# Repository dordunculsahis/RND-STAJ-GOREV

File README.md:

# TRANSCIEVER-FOOTPRINT
SN65HVD10 RS485 Transceiver'in SMD ve Through Hole footprintleri 'TRANSCEİVER.pretty' klasörünün içindedir

Transceiver'in schematic kütüphanesi 'TRANSCEİVER.lib' dosyasıdır.

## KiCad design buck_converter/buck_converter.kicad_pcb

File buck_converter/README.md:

Düşürücü tipli DC-DC dönüştürücü( Buck Converter)

dönüştürücünün schematic ve pcb dosyaları, bu dosyaları hazırlarken oluşturduğum symbol ve footprint kütüphaneleri eklendi

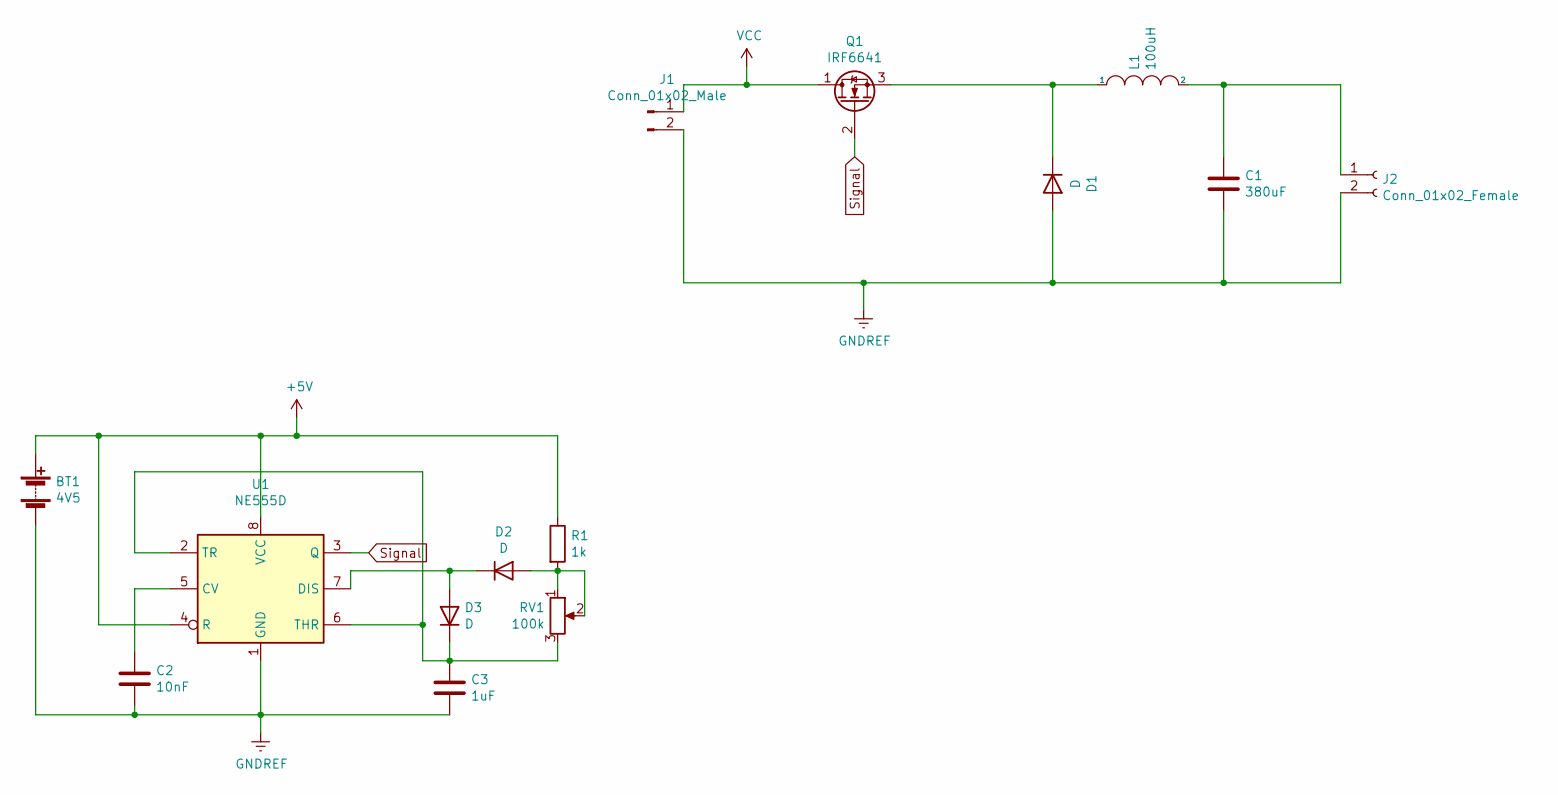
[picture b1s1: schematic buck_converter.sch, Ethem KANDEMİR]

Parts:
BT1: 4V5; BatteryHolder_Keystone_2479_3xAAA
C1: 380uF; C_0504_1310Metric
C2: 10nF; C_0504_1310Metric_Pad0.83x1.28mm_HandSolder
C3: 1uF; C_0504_1310Metric_Pad0.83x1.28mm_HandSolder
D1: D; D_0201_0603Metric
D2, D3: D; D_0201_0603Metric_Pad0.64x0.40mm_HandSolder
J1: Conn_01x02_Male; PinHeader_1x02_P1.27mm_Vertical
J2: Conn_01x02_Female; PinSocket_1x02_P1.00mm_Vertical
L1: 100uH; L_0805_2012Metric
Q1: IRF6641; DirectFET_MZ
R1: 1k; R_0402_1005Metric_Pad0.72x0.64mm_HandSolder
RV1: 100k; Potentiometer_ACP_CA9-VSMD_Vertical_Hole
U1: NE555D; SOIC-8_3.9x4.9mm_P1.27mm

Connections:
+5V: BT1.1 (+), R1.1, U1.4 (R), U1.8 (VCC)
GNDREF: BT1.2 (-), C1.2, C2.2, C3.2, D1.2 (A), J1.2, J2.2, U1.1 (GND)
unnamed: C1.1, J2.1, L1.2
unnamed: C2.1, U1.5 (CV)
unnamed: C3.1, D3.1 (K), RV1.3, U1.2 (TR), U1.6 (THR)
unnamed: D1.1 (K), L1.1, Q1.3 (S)
unnamed: D2.1 (K), D3.2 (A), U1.7 (DIS)
unnamed: D2.2 (A), R1.2, RV1.1, RV1.2
Signal: Q1.2 (G), U1.3 (Q)
VCC: J1.1, Q1.1 (D)

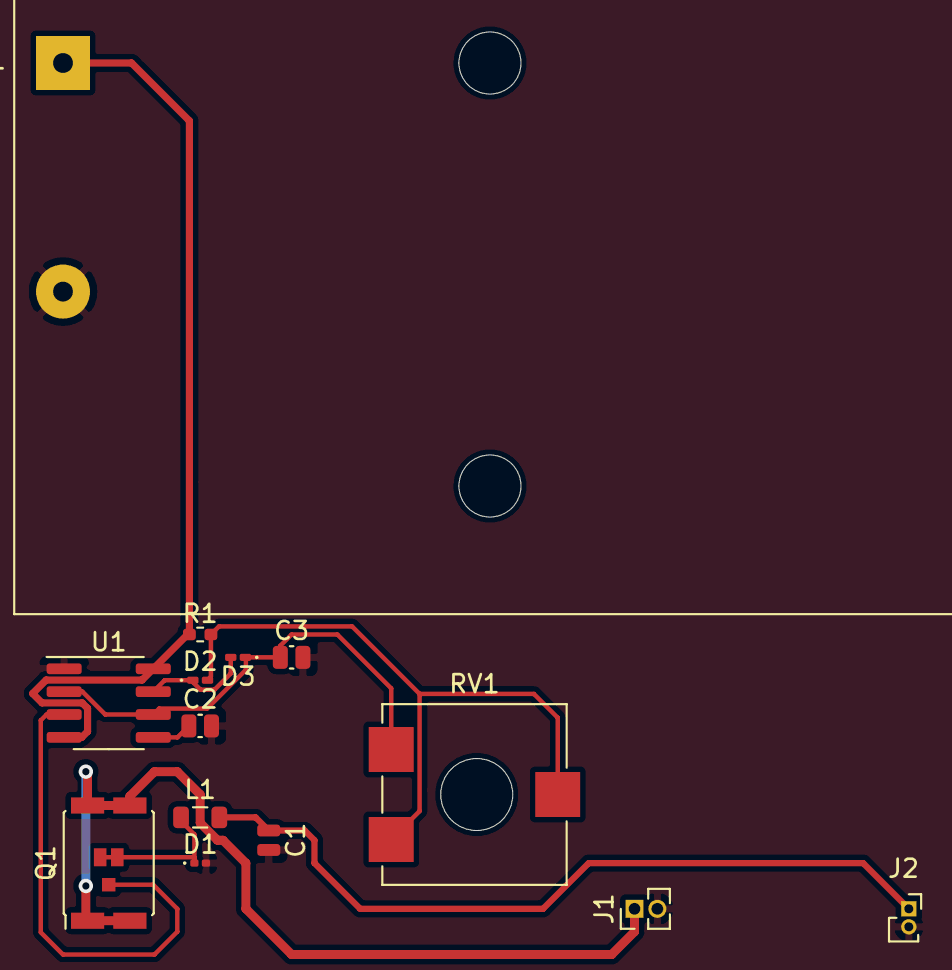
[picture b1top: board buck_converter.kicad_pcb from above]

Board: 2 copper layers, 14 parts (0 on the bottom side), 10 nets.

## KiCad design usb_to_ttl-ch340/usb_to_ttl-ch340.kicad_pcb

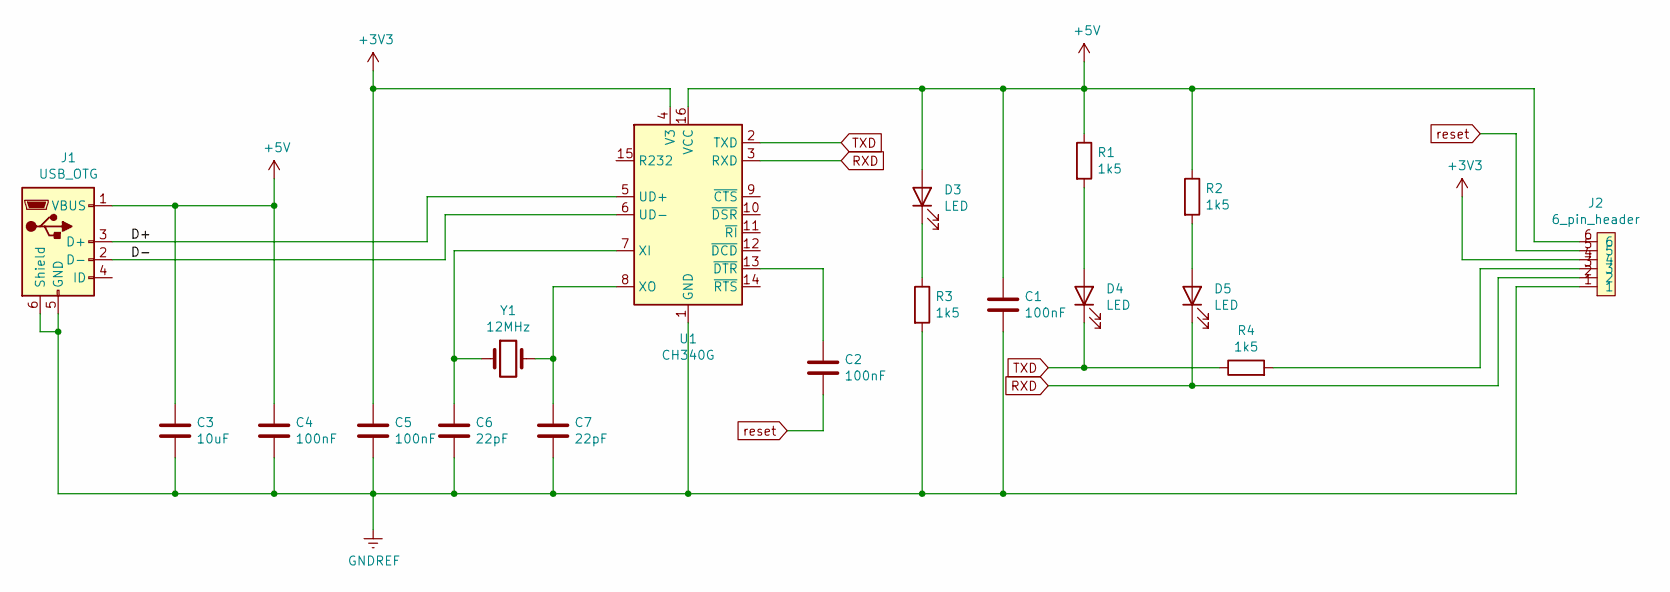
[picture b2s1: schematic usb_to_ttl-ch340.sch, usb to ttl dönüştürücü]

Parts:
C1, C2, C4, C5: 100nF; C_0201_0603Metric_Pad0.64x0.40mm_HandSolder
C3: 10uF; C_0201_0603Metric_Pad0.64x0.40mm_HandSolder
C6, C7: 22pF; C_0201_0603Metric_Pad0.64x0.40mm_HandSolder
D3, D4, D5: LED; LED_0201_0603Metric
J1: USB_OTG; USB_Micro-B_Molex-105017-0001
J2: 6_pin_header; PinHeader_1x06_P1.00mm_Horizontal
R1, R2, R3, R4: 1k5; R_0201_0603Metric_Pad0.64x0.40mm_HandSolder
U1: CH340G; SOIC-16_3.9x9.9mm_P1.27mm
Y1: 12MHz; Crystal_SMD_HC49-SD

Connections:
+3V3: C5.1, J2.4, U1.4 (V3)
+5V: C1.1, C3.1, C4.1, D3.2 (A), J1.1 (VBUS), J2.6, R1.1, R2.1, U1.16 (VCC)
/D+: J1.3 (D+), U1.5 (UD+)
/D-: J1.2 (D-), U1.6 (UD-)
GNDREF: C1.2, C3.2, C4.2, C5.2, C6.2, C7.2, J1.5 (GND), J1.6 (Shield), J2.1, R3.2, U1.1 (GND)
unnamed: C2.1, U1.13 (~DTR)
unnamed: C6.1, U1.7 (XI), Y1.1
unnamed: C7.1, U1.8 (XO), Y1.2
unnamed: D3.1 (K), R3.1
unnamed: D4.2 (A), R1.2
unnamed: D5.2 (A), R2.2
unnamed: J2.3, R4.2
RXD: D5.1 (K), J2.2, U1.3 (RXD)
TXD: D4.1 (K), R4.1, U1.2 (TXD)
reset: C2.2, J2.5

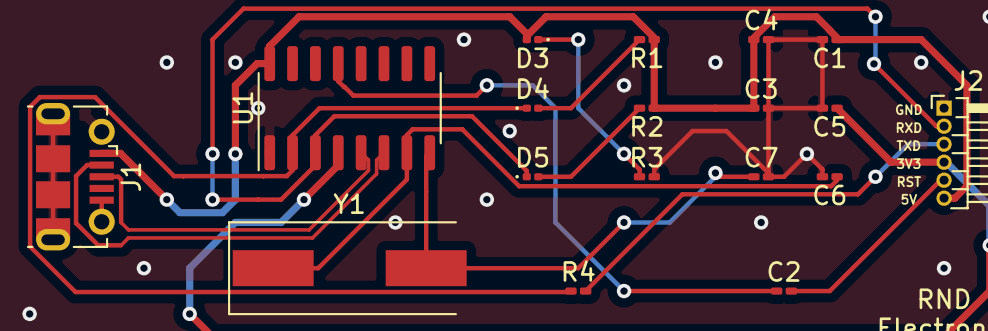
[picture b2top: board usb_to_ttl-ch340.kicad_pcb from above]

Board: 2 copper layers, 18 parts (0 on the bottom side), 15 nets.

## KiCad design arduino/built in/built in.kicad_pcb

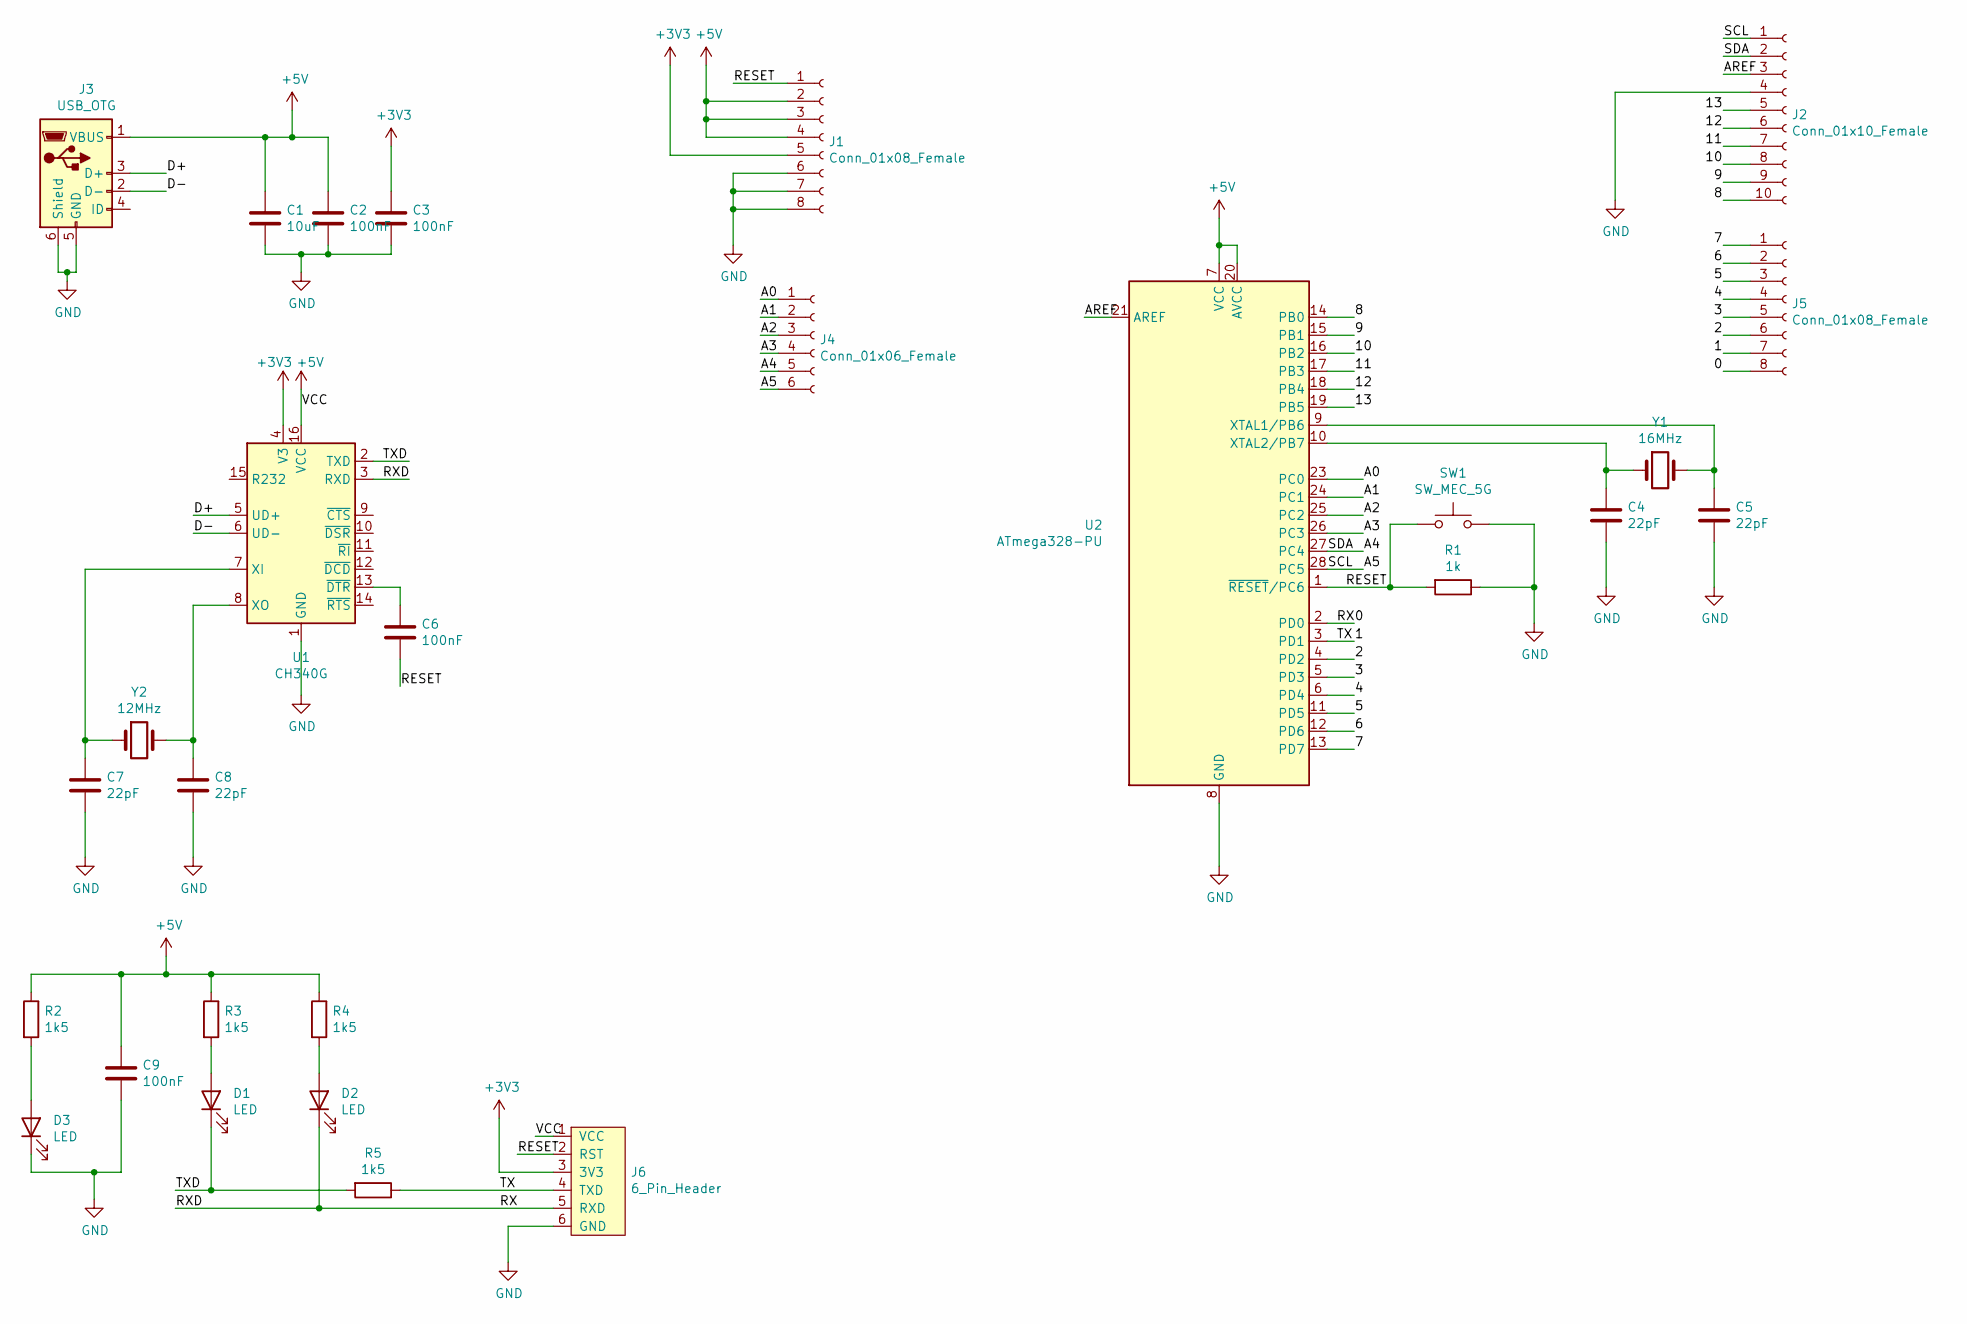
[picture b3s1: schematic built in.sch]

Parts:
C1: 10uF; CP_EIA-1608-08_AVX-J
C2, C3, C6, C9: 100nF; CP_EIA-1608-08_AVX-J
C4, C5, C7, C8: 22pF; CP_EIA-1608-08_AVX-J
D1, D2, D3: LED; LED_0201_0603Metric
J1, J5: Conn_01x08_Female; PinSocket_1x08_P1.27mm_Vertical
J2: Conn_01x10_Female; PinSocket_1x10_P1.27mm_Vertical
J3: USB_OTG; USB_Micro-B_Molex-105017-0001
J4: Conn_01x06_Female; PinSocket_1x06_P1.27mm_Vertical
J6: 6_Pin_Header; PinHeader_2x03_P1.27mm_Vertical
R1: 1k; R_0201_0603Metric
R2, R3, R4, R5: 1k5; R_0201_0603Metric
SW1: SW_MEC_5G; SW_MEC_5GSH9
U1: CH340G; SOIC-16_3.9x9.9mm_P1.27mm
U2: ATmega328-PU; DIP-28_W7.62mm
Y1: 16MHz; Crystal_HC18-U_Vertical
Y2: 12MHz; Crystal_HC18-U_Vertical

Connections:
+3V3: C3.1, J1.5, J6.3 (3V3), U1.4 (V3)
+5V: C1.1, C2.1, C9.1, J1.2, J1.3, J1.4, J3.1 (VBUS), J6.1 (VCC), R2.1, R3.1, R4.1, U1.16 (VCC), U2.7 (VCC), U2.20 (AVCC)
/0: D2.1 (K), J5.8, J6.5 (RXD), U1.3 (RXD), U2.2 (PD0)
/1: J5.7, J6.4 (TXD), R5.1, U2.3 (PD1)
/2: J5.6, U2.4 (PD2)
/3: J5.5, U2.5 (PD3)
/4: J5.4, U2.6 (PD4)
/5: J5.3, U2.11 (PD5)
/6: J5.2, U2.12 (PD6)
/7: J5.1, U2.13 (PD7)
/8: J2.10, U2.14 (PB0)
/9: J2.9, U2.15 (PB1)
/10: J2.8, U2.16 (PB2)
/11: J2.7, U2.17 (PB3)
/12: J2.6, U2.18 (PB4)
/13: J2.5, U2.19 (PB5)
/A0: J4.1, U2.23 (PC0)
/A1: J4.2, U2.24 (PC1)
/A2: J4.3, U2.25 (PC2)
/A3: J4.4, U2.26 (PC3)
/A4: J2.2, J4.5, U2.27 (PC4)
/A5: J2.1, J4.6, U2.28 (PC5)
/AREF: J2.3, U2.21 (AREF)
/D+: J3.3 (D+), U1.5 (UD+)
/D-: J3.2 (D-), U1.6 (UD-)
/RESET: C6.2, J1.1, J6.2 (RST), R1.2, SW1.1 (A), SW1.2 (A), U2.1 (~RESET~/PC6)
/TXD: D1.1 (K), R5.2, U1.2 (TXD)
GND: C1.2, C2.2, C3.2, C4.2, C5.2, C7.2, C8.2, C9.2, D3.1 (K), J1.6, J1.7, J1.8, J2.4, J3.5 (GND), J3.6 (Shield), J6.6 (GND), R1.1, SW1.3 (B), SW1.4 (B), U1.1 (GND), U2.8 (GND), U2.22 (GND)
unnamed: C4.1, U2.10 (XTAL2/PB7), Y1.1
unnamed: C5.1, U2.9 (XTAL1/PB6), Y1.2
unnamed: C6.1, U1.13 (~DTR)
unnamed: C7.1, U1.7 (XI), Y2.1
unnamed: C8.1, U1.8 (XO), Y2.2
unnamed: D1.2 (A), R3.2
unnamed: D2.2 (A), R4.2
unnamed: D3.2 (A), R2.2

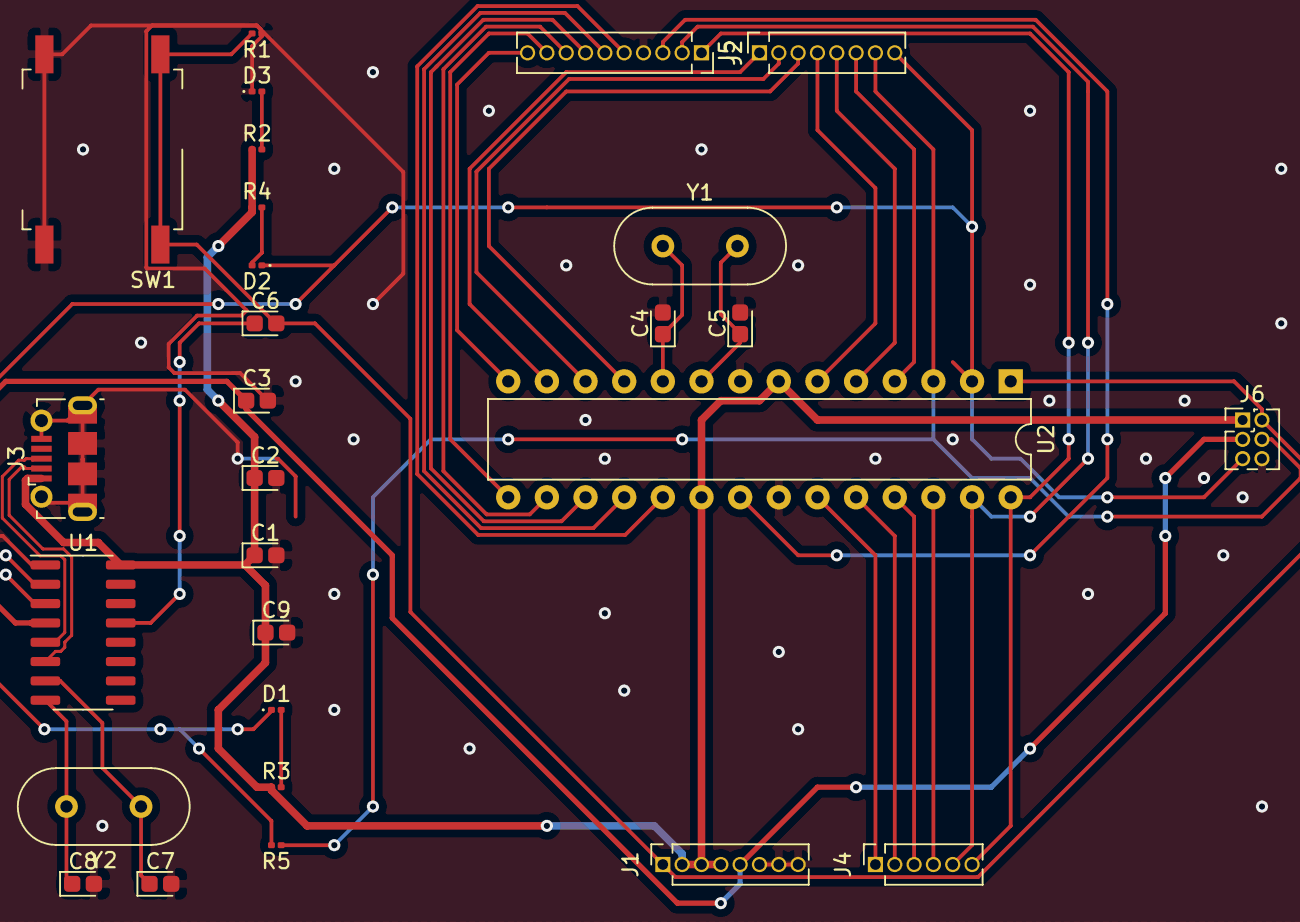
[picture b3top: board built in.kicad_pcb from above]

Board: 2 copper layers, 28 parts (0 on the bottom side), 36 nets.

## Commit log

2021-08-18 oluşturma
    SN65HVD10D RS485 Transceiver(SOIC) ve SN65HVD10P RS485 Transceiver(PDIP) footprint ve schematic library dosyaları
2021-08-19 Düzeltme
    schematic libraryde yapılan pin hataları düzeltildi
2021-08-20 rapor
2021-08-20 BATTERY PROTECTION
2021-08-20 yeniden oluşturma
    yeni branch oluştururken bir hata yaptığım için silinen dosyaları yeniden ekledim
2021-08-20 BATTERY PROTECTION (#2)
2021-08-20 HATA
2021-08-20 DÜZELTME
2021-08-20 BATTERY PROTECTION OLUŞTURMA
    'battery protection.lib' dosyası schematic librarydir. 'battery protection.pretty' klasörü footprint librarydir
2021-08-20 düzenleme
2021-08-20 raporlama
    projenin raporunu ekledim
2021-08-22 GSM-GPRS MODULE oluşturma
2021-08-25 Create Ethem_Kandemir_Gsm_modül_Rapor.docx
    proje raporu oluşturuldu
2021-08-30 create: buck_converter
2021-09-05 create:usb_to_ttl
    projenin schematic tasarımı tamamlandı ancak pcb bağlantıları henüz tamamlanmadı
2021-09-07 güncelleme
2021-09-07 düzeltme 2
2021-09-07 düzeltme3
2021-09-09 son güncelleme
    pcb tasarımında bazı ufak değişiklikler yapıldı .
    sayfa ayarları yapıldı
2021-09-09 güncelleme
    kontrol edilmeyecek de olsa hatalı olduğumu belirttiğiniz noktaları düzeltmeye çalıştım
2021-09-09 güncelleme
    gereksiz olan kütüphaneler silindi
2021-09-10 düzeltme
    belirtilen hatalar giderilmeye çalışıldı
2021-09-10 diffferential pair
2021-09-17 arduino built in ilk oluşturma
2021-09-17 yol kalınlığı
    projelerde pcb yol kalınlıkları akım kapasitelerine göre yeniden düzenlendi
